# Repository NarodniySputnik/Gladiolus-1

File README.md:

# Проект Gladiolus-1 (Народный Спутник)
<div align="center"></div>

Мы - команда радиолюбителей-энтузиастов под руководством Дмитрия R4UAB Пашкова!
В данный момент мы работаем над проектом "Народный спутник"! 
Наша цель - это создание функционального малого космического аппарата (CubeSat) для популяризации радиолюбительства, как интересного и увлекательного занятия для людей всех возрастов. Проект создаётся полностью на добровольных началах и заинтересованности наших участников. 

Наши задачи: 

- Реализовать полный цикл создания малого космического аппарата CubeSat - от проектирования и сборки до запуска и работы на орбите. 
- Предоставить открытые данные и существующие наработки по проекту для всех желающих, вдохновить всех любителей космической тематики и радиолюбителей на разработку и участие в новых интересных технологических проектах. 
- Объединить единомышленников для практической работы в области космических технологий и радиосвязи.

С огромнейшим удовольствием примем в нашу команду всех кто может и хочет приложить руку к созданию реального космического аппарата!

We are a team of amateur radio enthusiasts led by Dmitry "R4UAB" Pashkov!
We are currently working on the "People's Satellite" project! Our goal is to create a functional small spacecraft (CubeSat) to popularize amateur radio as an interesting and engaging activity for people of all ages. The project is being developed entirely on a voluntary basis and based on the passion of our participants.

Our goals:

- Implement the full development cycle of the CubeSat small spacecraft-from design and assembly to launch and operation in orbit.
- Provide open data and existing project developments to everyone, inspiring all space enthusiasts and radio amateurs to develop and participate in new exciting technological projects.
- Bring together like-minded individuals for practical work in the field of space technology and radio communications.

We are delighted to welcome anyone who can and wants to contribute to the creation of a real spacecraft to our team!

## Структура директорий
- doc - Документы
	- ds - Технические спецификации
	- img - Изображения
	- info - Информация
	- ref - Референсы и примеры
- firmware - Прошивки
- hardware - Печатные платы и схемы
	- library - Библиотеки KiCad
- software - Программы

## Назначение модуля
Gladiolus-1 - автономный модуль для приема и передачи изображений в формате SSTV (Slow Scan TeleVision) на малом космическом аппарате (МКА) формата CubeSat

1.2. Основание для разработки
Решение технического комитета проекта «Gladiolus-1» 

1.3. Назначение
Создание функциональной полезной нагрузки для:

Приёма команд с Земли <br>
Съёмки поверхности Земли <br>
Генерации и передачи изображений в формате SSTV <br>
Приёма и ретрансляции цифровых пакетных данных <br>
Проведения образовательных и научных экспериментов

1.4. Краткое описание системы<br>
Полезная нагрузка представляет собой модульную систему, построенную на основе единой шинной архитектуры. Система включает в себя два вычислительных блока различной архитектуры, обеспечивающих резервирование и распределение функций, два идентичных модемных блока с возможностью взаимозамены, центральный блок управления питанием и данными, а также антенную систему.

2. ОБЩИЕ ТРЕБОВАНИЯ

2.1. Эксплуатационные характеристики

<div align="left">
<table>
<tr><td>Формат:</td><td>CubeSat 1U (габариты 100×100×113,5 мм)</td></tr>
<tr><td>Орбита:</td><td>Низкая околоземная орбита (высота 500–600 км), солнечно-синхронная</td></tr>
<tr><td>Энергопотребление среднее:</td><td>не более 2Вт</td></tr>
<tr><td>Энергопотребление пиковое:</td><td>Не более 5Вт</td></tr>
<tr><td>Масса:</td><td>Не более 1.33кг</td></tr>
<tr><td>Габариты:</td><td>Соответствуют стандарту CubeSat 1U</td></tr>
</table></div>
Режимы работы должны обеспечивать положительный энергобаланс

2.2. Условия эксплуатации

<div align="left">
<table>
<tr><td>Температурный диапазон:</td><td>–40°C до +80°</td></tr>
<tr><td>Вибронагрузки:</td><td>Соответствуют стандартам запуска CubeSat</td></tr>
<tr><td>Ударные нагрузки:</td><td>До 100g</td></tr>
<tr><td>Вакуум:</td><td>До 10⁻⁶ Торр</td></tr>
<tr><td>Радиационная стойкость:</td><td>Критическая накопленная доза облучения 20 крад (Si)</td></tr>
</table></div>

2.3. Интерфейсы с платформой спутника
<div align="left"><table>
<tr><td>Питание:</td><td>Напряжение шины питания 3.2-8.4 В, ток до 1 А</td></tr>
<tr><td>Механический интерфейс:</td><td>Стандартные крепления CubeSat</td></tr>
<tr><td>Тепловой интерфейс:</td><td>Кондуктивный отвод тепла на платформу</td></tr>
<tr><td>Другие интерфейсы:</td><td>Не предусмотрены</td></tr>

</table></div>

3. ФУНКЦИОНАЛЬНОЕ ДЕЛЕНИЕ И ТРЕБОВАНИЯ К БЛОКАМ

3.1. БЦВМ 1 (Бортовая Цифровая Вычислительная Машина 1)

3.1.1. Аппаратная платформа:

<div align="left"><table>
<tr><td>Основной процессор:</td><td>Raspberry Pi Zero v1.3</td></tr>
<tr><td>Память:</td><td>Оперативная 512 МБ, флеш-память microSD</td></tr>
<tr><td>Тактовая частота:</td><td>Программно регулируемая от минимальной до номинальной</td></tr>
<tr><td>Отключаемые интерфейсы:</td><td>USB, HDMI, ненужные периферийные модули</td></tr>
</table></div>

3.1.2. Функции:

<div align="left">
<table>
<tr><td>Управление файловой системой бортового накопителя</td></tr>
<tr><td>Общее управление системой и координация работы блоков</td></tr>
<tr><td>Обработка команд и телеметрии</td></tr>
<tr><td>Маршрутизация данных между подсистемами</td></tr>
<tr><td>Резервная функция программной генерации сигнала SSTV</td></tr>
<tr><td>Ведение журнала работы системы</td></tr>
</table></div>

3.1.3. Интерфейсы:

<div align="left">
<table>
<tr><td>1× 40-контактный разъем для подключения к материнской плате</td></tr>
<tr><td>Поддержка шин RS-485 и I2C</td></tr>
</table></div>

3.2. БЦВМ 2 (Бортовая Цифровая Вычислительная Машина 2)

3.2.1. Аппаратная платформа: <br>
Основной микроконтроллер: STM32 серии (конкретная модель по результатам анализа) <br>
Периферия: <br>
Встроенный RTC с независимым питанием <br>
Интерфейс DCMI для подключения камеры <br>
2× UART для шин RS-485 <br>
Интерфейсы I2C, SPI для дополнительной периферии <br>
Внешняя SPI-Flash или SD-карта для хранения данных <br>
Режимы работы: Поддержка энергоэффективных режимов <br>

3.2.2. Функции:
Управление камерой: инициализация, захват кадра, настройка параметров <br>
Обработка изображений и подготовка данных для передачи в формате SSTV <br>
Управление SSTV-передатчиком <br>
Синхронизация операций по времени с помощью RTC <br>
Дублирующее управление бортовым накопителем <br>
Резервирование критических функций БЦВМ 1 <br>

3.2.3. Взаимодействие между БЦВМ:
Обмен данными через единые шины RS-485 <br>
Взаимный мониторинг состояния и работоспособности <br>
Автоматическое перераспределение функций при отказах <br>
Синхронизация времени и планирование задач

3.3. Модемный блок (в количестве 2 шт.)
3.3.1. Аппаратная основа:

<div align="left"><table>
<tr><td>Радиомодули:</td><td>На каждый блок: Ra-02 (на основе SX1278)</td></tr>
<tr><td>Усилители:</td><td>МШУ на приём, усилитель AB-IOT-433 передачу</td></tr>
<tr><td>Фильтры:</td><td>ПАВ-фильтры на приём и передачу</td></tr>
<tr><td>Согласующие цепи:</td><td>Wideband matching networks</td></tr>
<tr><td>Микроконтроллер:</td><td>MSP430FR5994IPNR</td></tr>
</table></div>

3.3.2. Функциональное назначение:

<div align="left">
<table>
<tr><td>Радиомодуль 1:</td><td>SSTV передатчик (ЧМ модуляция, 438МГц)</td></tr>
<tr><td>Радиомодуль 2:</td><td>Цифровая радиолиния (435Мгц)</td></tr>
<tr><td>Резервирование:</td><td>Возможность переконфигурации модулей</td></tr>
</table></div>

3.3.3. Электрические параметры:

<div align="left">
<table>
<tr><td>Мощность передатчика:</td><td>До 2Вт (регулируемая)</td></tr>
<tr><td>Чувствительность приёмника:</td><td>Не хуже -130dBm</td></tr>
<tr><td>Стабильность частоты:</td><td>±1 ppm</td></tr>
<tr><td>Потребляемый ток:</td><td>Передача ≤ 500 мА, прием ≤ 50 мА</td></tr>
</table></div>

3.3.4. Дополнительные функции:
Контроль температуры через I2C<br>
Мониторинг параметров усилителей<br>
Защита от КЗ и перегрева<br>
Автоматическая калибровка

3.4. Материнский блок (Блок управления питанием и данными)

3.4.1. Система питания:

<div align="left"><table>
<tr><td>Вход:</td><td>3.2-8.4В от платформы спутника</td></tr>
<tr><td>Выход:</td><td>Стабилизированное +5В через интеллектуальные ключи</td></tr>
<tr><td>КПД:</td><td>Не менее 90% при номинальной нагрузке</td></tr>
<tr><td>Защите:</td><td>Ограничение тока, защита от КЗ, от перенапряжения</td></tr>
</table></div>

3.4.2. Управление и мониторинг:

<div align="left">
<table>
<tr><td>Централизованный сбор телеметрии через I2C</td></tr>
<tr><td>Управление питанием каждого блока</td></tr>
<tr><td>Аппаратный watchdog (MAX6301)</td></tr>
<tr><td>Счетчик перезагрузок в энергонезависимой памяти</td></tr>
</table></div>

3.4.3. Интерфейсы:

<div align="left">
<table>
<tr><td>4× 40-контактных разъема для функциональных блоков</td></tr>
<tr><td>2× шины RS-485 с протоколом AX.25</td></tr>
<tr><td>Шина I2C с мультиплексором для изоляции подключенных блоков</td></tr>
</table></div>

3.4.4. Система I2C мультиплексирования:
Архитектура: Мультиплексор I2C с 8 и более каналами

Назначение каналов:

<div align="left">
<table>
<tr><td>Канал 0:</td><td>Внутренние датчики материнского блока</td></tr>
<tr><td>Канал 1:</td><td>БЦВМ</td></tr>
<tr><td>Канал 2:</td><td>БЦВМ</td></tr>
<tr><td>Канал 3:</td><td>Модемный блок 1</td></tr>
<tr><td>Канал 4:</td><td>Модемный блок 2</td></tr>
<tr><td>Канал 5:</td><td>Резерв</td></tr>
<tr><td>Канал 6:</td><td>Резерв</td></tr>
<tr><td>Канал 7:</td><td>Резерв</td></tr>
</table></div>

<div align="left">
<table>
<tr><td>Управление:</td><td>Программное переключение каналов мультиплексора</td></tr>
<tr><td>Восстановление:</td><td>Автоматический сброс зависших устройств</td></tr>
</table></div>

3.4.5. Мониторинг питания: <br>
Детектирование аварий: Мониторинг напряжения на линии PWR_FAULT <br>
Реакция на аварии: Автоматическое отключение питания блока при аварии <br>
Логирование: Запись событий аварий питания

3.5. Антенный блок
<div align="left"><table>
<tr><td>Диапазоны:</td><td>435 и 438МГц</td></tr>
<tr><td>Поляризация:</td><td>Линейная</td></tr>
<tr><td>КСВ:</td><td>Не более 1.5 в рабочем диапазоне</td></tr>
<tr><td>Конструктив:</td><td>Складываемая конструкция, совместимая с 1U CubeSat</td></tr>
<tr><td>Коэффициент усиления:</td><td>Не менее 0 dBi для каждого диапазона</td></tr>
<td>Диаграмма направленности:</td><td>Широконаправленная для обеспечения связи при различных ориентациях спутника</td></tr>
</table></div>

3.6. Требования к унификации блоков

3.6.1. Стандартизация разъемов:<br>
Единый 40-контактный разъем для всех блоков <br>
Фиксированная распиновка (см. Таблицу 1) <br>
Механическая фиксация от самопроизвольного отключения

Таблица 1. Распиновка 40-контактного разъема
<div align="left">
<table>
<tr>
<th>Контакты</th><th>Назначение</th><th>Описание</th></tr>
<tr><td>1-4</td><td>+5V</td><td>Питание +5В</td></tr>
<tr><th>5-8</th><th>GND</th><th>Земля</th></tr>
<tr><td>I2C</td><td>SCL</td><td>SCL</td></tr>
<tr><td>I2C</td><td>SDA</td><td>SDA</td></tr>
<tr><td>I2C_PWR</td><td></td><td>Плюс питания</td></tr>
<tr><td>I2C_GND</td><td></td><td>Земля</td></tr>
<tr><td>A1, B2</td><td>RS-485</td><td>2 контакта</td></tr>
<tr><td>PWR_EN</td><td>управление</td><td>включение питания</td></tr>
<tr><td>RESET</td><td>Сброс</td><td>включение питания</td></tr>
<tr><td>PWR_FAULT</td><td>Мониторинг</td><td>1 контакт</td></tr>
<tr><td>PWR_FAULT</td><td>Резерв</td><td>21 контакт</td></tr>
</table></div>

3.6.2. Организация шин:<br>
Параллельное подключение всех блоков к общим шинам<br>
Индивидуальное управление питанием<br>
Единые протоколы обмена

4. ТРЕБОВАНИЯ К ИНТЕРФЕЙСАМ И ПРОТОКОЛАМ

4.1. Физический уровень
RS-485: Двухпроводная дифференциальная шина<br>
Скорость: 1200-2000000 бод<br>
I2C: Стандартный протокол с тактовой частотой до 400 кГц (Fast Mode)

<div align="left"><table>
<tr><td>RS-485</td><td>Двухпроводная дифференциальная шина</td></tr>
<tr><td>Скорость:</td><td>1200-2000000 бод</td></tr>
<tr><td>I2C</td><td>Стандартный протокол с тактовой частотой до 400 кГц</td></tr>
</table></div>

4.2. Протокол обмена

<div align="left"><table>
<tr><td>Базовый протокол</td><td>AX.25</td></tr>
<tr><td>Формат пакетов</td><td>HDLC-like frame structure</td></tr>
<tr><td>Контроль ошибок</td><td>CRC-16</td></tr>
<tr><td>Адресация</td><td>расширенная схема адресации подсистем</td></tr>
</table></div>

4.3. Логика работы <br>
Широковещательная и адресная передача <br>
Подтверждение приема критических команд <br>
Повторная передача при ошибках <br>
Приоритезация пакетов

4.4. Протокол обмена по I2C

<div align="left"><table><tr>
<td>Адресация устройств</td><td>7-битная схема адресации</td></tr>
<tr><td>Скорость обмена</td><td>до 400 кбит/сек</td></tr>
<tr><td>Формат сообщений</td><td>Управляющие команды <br> Данные телеметрии <br> Статусные сообщения</td></tr>
<tr><td>Арбитраж</td><td>Автоматическое разрешение коллизий</td></tr>
<tr><td>Таймауты</td><td>Защита от зависания шины</td></tr>
</table></div>

5. МЕХАНИЧЕСКИЕ И КОНСТРУКТИВНЫЕ ТРЕБОВАНИЯ

5.1. Компоновка

<div align="left"><table>
<tr><td>Формат</td><td>1U CubeSat (100x100x113, 5мм)</td></tr>
<tr><td>Количество плат:</td><td>3-4 печатных платы в стэке</td></tr>
<tr><td>Высота компонентов:</td><td>С учётом зазора между платами</td></tr>
</table></div>

5.2. Материалы

<div align="left"><table>
<tr><td>Основа плат:</td><td>FR-4 c Tg ≥ 170°C</td></tr>
<tr><td>Покрытие:</td><td>Конформное покрытие для защиты от влаги и загрязнений</td></tr>
<tr><td>Защитные покрытия:</td><td>Использование металлов без защитного покрытия не допускается. Все металлические поверхности должны иметь защитное покрытие для функционирования в космических условиях</td></tr>
<tr><td>Монтажные компоненты:</td><td>Использование оловянно-свинцовых припоев (Sn63Pb37 или аналог). Бессвинцовые припои не допускаются.</td></tr>
</table></div>

5.3. Тепловой режим <br>
Пассивное охлаждение через корпус<br>
Распределение тепловыделяющих компонентов<br>
Тепловой контакт с платформой спутника

6. ТРЕБОВАНИЯ К НАДЁЖНОСТИ

6.1. Показатели надежности

<div align="left">
<table>
<tr><td>Средняя наработка на отказ:</td>
<td>≥ 10 000 часов</td></tr>
<tr><td>Вероятность безотказной работы:</td>
<td>≥ ≥ 0.95 за 1 год</td></tr>
<tr><td>Коэффициент готовности:</td>
<td>≥ 0.98</td></tr>
</table></div>

6.2. Радиационная стойкость

6.2.1. Критерии стойкости: <br>
Сохранение работоспособности до 20 крад (Si)<br>
Постепенная деградация параметров после 20 крад<br>
Сохранение базовой функциональности до 25 крад

6.2.2. Методы обеспечения: <br>
Выбор компонентов с подтвержденной стойкостью<br>
Локальные экраны для чувствительных элементов<br>
Схемная избыточность и резервирование<br>
RAD-HARD компоненты для критических узлов

6.2.3. Испытания: <br>
Радиационные испытания на ускорителях<br>
Контроль параметров при дозах 10, 15, 20, 25 крад<br>
Тестирование на SEE и SEL<br>
Термоциклирование после облучения

6.2.4. Расчетные параметры: <br>
Запас 20% относительно расчетной дозы<br>
Учет всех видов ионизирующего излучения<br>
Моделирование радиационной обстановки

7. ТРЕБОВАНИЯ К ОТЛАДОЧНОМУ ОБОРУДОВАНИЮ

7.1. Плата-удлинитель для внешней отладки

7.1.1. Конструкция: <br>
Печатная плата с посадочным местом для функционального блока<br>
Штатный 40-контактный разъем со стороны спутника<br>
Механическое крепление блока винтами<br>
Тестовые точки и защитные элементы

7.1.2. Параметры: <br>
Сопротивление проводников: ≤ 0.1 Ом
Рабочая температура: -40°C до +80°C
Стойкость к вибрациям согласно требованиям

<div align="left"><table>
<tr><td>Сопротивление проводников:</td><td> ≤ 0.1 Ом</td></tr>
<tr><td>Рабочая температура:</td><td>-40°C до +80°C</td></tr>
<tr><td>Стойкость к вибрациям:</td><td>Cогласно требованиям</td></tr>
</table></div>

7.2. Плата-эмулятор материнской платы <br>
7.2.1. Функционал:
Эмуляция штатной материнской платы<br>
Управление питанием подключенного блока<br>
Мониторинг токопотребления<br>
Организация шин RS-485 и I2C

7.2.2. Интерфейсы: <br>
1× 40-контактный разъем для блока<br>
USB Type-C для питания и связи<br>
JTAG для низкоуровневой отладки<br>

7.2.3. Программное обеспечение: <br>
Графическая утилита для управления<br>
Эмуляция штатных режимов работы<br>
Логирование и анализ данных<br>
Библиотека тестовых сценариев<br>
Мониторинг шины I2C в реальном времени

7.2.4. Технические характеристики:

<div align="left"><table>
<tr><td>Входное напряжение</td><td>12 В DC или USB-C</td></tr>
<tr><td>Выходной ток</td><td>До 2А</td></tr>
<tr><td>Поддержка скоростей RS-485:</td><td>1200 бод - 2 Мбод</td></tr>
<tr><td>Поддержка I2C:</td><td>Standard Mode (100 кГц), Fast Mode (400 кГц)</td></tr>
<tr><td>Рабочая температура:</td><td>0°C до +50°C</td></tr>
</table></div>

7.3. Совместимость <br>
Полная электрическая и программная совместимость<br>
Использование в термовакуумной камере<br>
Соответствие требованиям наземных испытаний

8. ЭТАПЫ РАЗРАБОТКИ И ИСПЫТАНИЙ

8.1. Основные этапы <br>
Эскизное проектирование<br>
Разработка конструкторской документации<br>
Изготовление опытных образцов<br>
Проведение испытаний<br>
Изготовление летного образца<br>
Сопровождение запуска и эксплуатации

8.2. Виды испытаний <br>
Вибродинамические<br>
Термовакуумные<br>
Радиационные<br>
Электромагнитная совместимость<br>
Функциональные и комплексные

8.3. Требования к вибродинамическим испытаниям
8.3.1. Условия проведения испытаний: <br>
Температура: +20°C ±5°C <br>
Относительная влажность: 40-60% <br>
Крепление образца: Штатные крепежные элементы, момент затяжки согласно конструкторской документации <br>

8.3.2. Режимы вибрационных испытаний:

<div align="left">
<table>
<tr><th>Синусоидальная вибрация</th></tr>
<tr><td>Диапазон частот:</td><td>5-100Гц</td></tr>
<tr><td>Амплитуда:</td><td>20g</td></tr>
<tr><td>Скорость развёртки:</td><td>2 октавы/мин</td></tr>
<tr><td>Направления:</td><td>X, Y, Z оси</td></tr>
<tr><td>Количество циклов:</td><td>3 цикла на каждое направление</td></tr>
<tr><th>Случайная вибрация</th></tr>
<tr><td>Диапазон частот:</td><td>20-2000Гц</td></tr>
<tr><td>Спектральная плотность 20-100Гц</td><td>+3 дБ/окт</td></tr>
<tr><td>Спектральная плотность 100-700Гц</td><td>0.04 g²/Гц</td></tr>
<tr><td>Спектральная плотность 700-2000Гц</td><td>-3 дБ/окт</td></tr>
<tr><td>Общее СКУ ускорение</td><td>7.7 g (среднеквадратичное)</td></tr>
<tr><td>Длительность:</td><td>2 минуты на каждое направление</td></tr>
<tr><td>Направления:</td><td>X, Y, Z оси</td></tr>
</table></div>

8.3.3. Контроль во время испытаний: <br>
Непрерывный мониторинг электрических параметров<br>
Регистрация резонансных частот<br>
Визуальный контроль после каждого этапа испытаний<

8.3.4. Критерии успешного прохождения: <br>
Отсутствие механических повреждений<br>
Сохранение функциональности системы<br>
Отсутствие необратимых изменений параметров<br>
Соответствие резонансных частот требованиям конструкции

8.4. Требования к термовакуумным испытаниям

8.4.1. Условия проведения испытаний:

<div align="left">
<table>
<tr><td>Вакуум:</td><td>≤ 10⁻⁵ Торр</td></tr>
<tr><td>Температурный диапазон:</td><td>-40°C до +80°C</td></tr>
<tr><td>Скорость изменения температуры:</td><td>не более 5°C/мин</td></tr>
<tr><td>Температурные датчики:</td><td>не менее 6 точек контроля</td></tr>
</table></div>

8.4.2. Профиль температурных циклов:

<div align="left">
<table>
<tr><th>Квалификационные испытания</th></tr>
<tr><td>Количество циклов:</td><td>8 циклов</td></tr>
<tr><td>Выдержка на экстремумах:</td><td>4 часа</td></tr>
<tr><td>Температурный диапазон:</td><td>-45°C до +85°C</td></tr>
<tr><th>Приёмо-сдаточные испытания</th></tr>
<tr><td>Количество циклов:</td><td>4 цикла</td></tr>
<tr><td>Выдержка на экстремумах:</td><td>2 часа</td></tr>
<tr><td>Температурный диапазон:</td><td>-40°C до +80°C</td></tr>
</table></div>

8.4.3. Контроль параметров: <br>
Электрические параметры: <br>
Потребляемый ток в различных режимах<br>
Стабильность напряжений питания<br>
Работоспособность интерфейсов связи<br>
Функциональные проверки:<br>
Проверка работы камеры на всех температурах<br>
Тестирование радиоканалов<br>
Проверка систем обработки данных

8.4.4. Тепловой баланс:

<div align="left"><table>
<tr><td>Мощность нагревателей:</td><td>регулируемая, с точностью ±1°C</td></tr>
<tr><td>Охлаждение:</td><td>жидкий азот или механическое охлаждение</td></tr>
<tr><td>Стабилизация температуры:</td><td>±2°C от заданной</td></tr>
</table></div>

8.4.5. Критерии успешного прохождения: <br>
Отсутствие деградации материалов и покрытий в вакууме (улетучивания, растрескивания)<br>
Сохранение герметичности компонентов<br>
Стабильность электрических параметров в течение всего цикла<br>
Отсутствие сбоев в работе программного обеспечения<br>
Сохранение механической целостности после термических расширений/сжатий<br>
Соответствие тепловых режимов расчетным значениям

## Состав команды | Team members

### Руководитель проекта | Team leader
- @r4uab

### Главный Конструктор | Chief Designer
- AnatoliySV

### Разработка антенны | Antenna development
- @stellar_alice
- @SV2HWM
- @Esprit_bel

### Разработка радиотракта | Radio path development
- @ub1qbm
- @PhaseShifting
- @ub8qbd

### Экспертная команда | Expert team
- @R2FAL
- @baskiton
- @RA3PPY

### Технические писатели | Technical writers
- @Esprit_bel

### Программисты | Programmers
- @cugadese

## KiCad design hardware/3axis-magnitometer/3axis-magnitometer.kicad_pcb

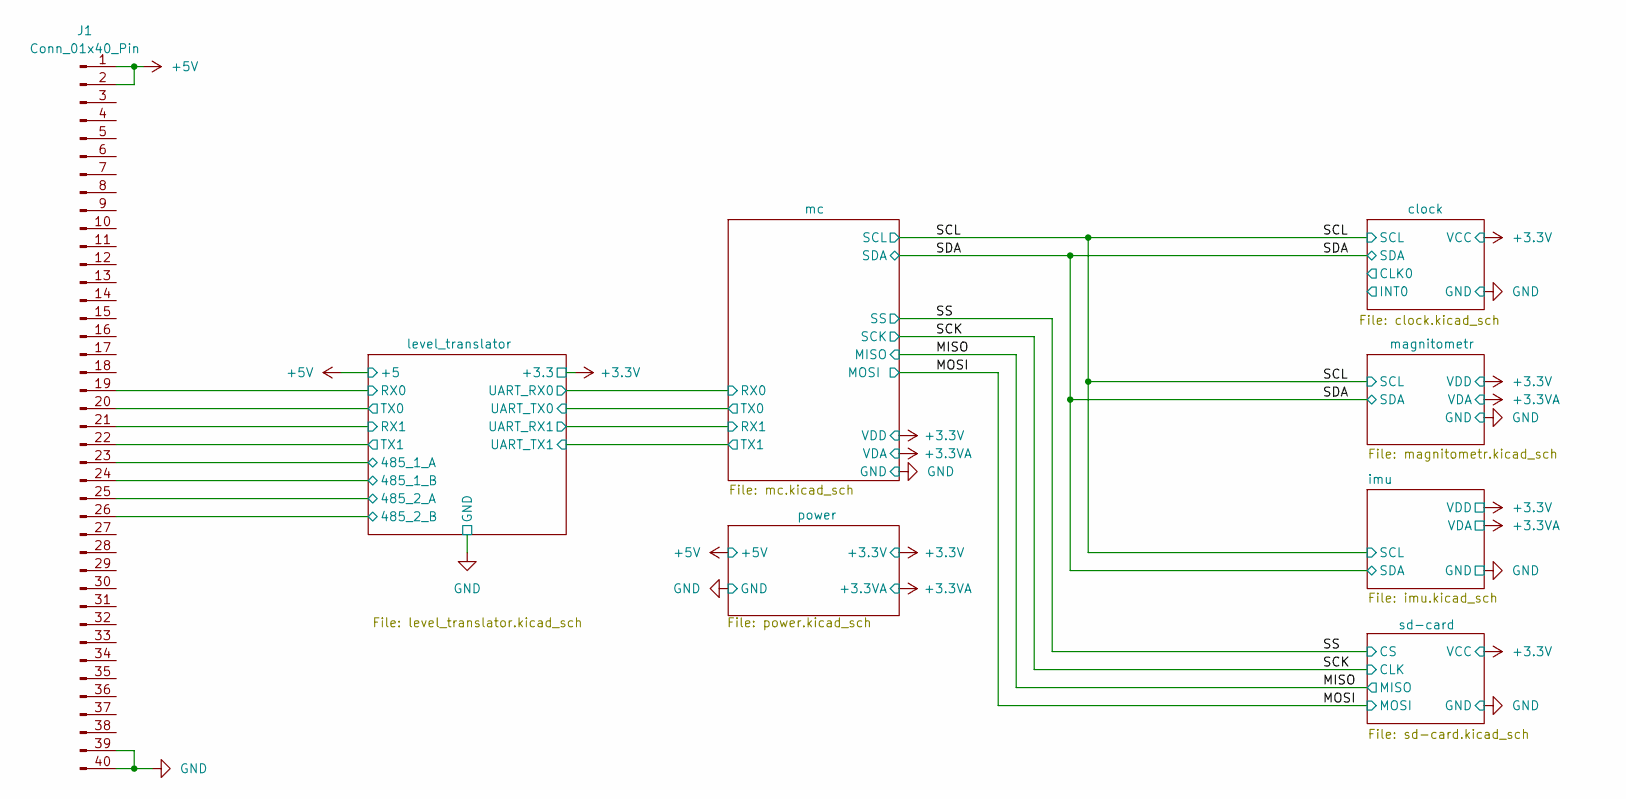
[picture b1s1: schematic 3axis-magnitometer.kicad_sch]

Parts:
J1: Conn_01x40_Pin; PinHeader_2x20_P2.54mm_Horizontal

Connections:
+5V: J1.1, J1.2; also elsewhere on the board
/level_translator/485_1_A: J1.23; also elsewhere on the board
/level_translator/485_1_B: J1.24; also elsewhere on the board
/level_translator/485_2_A: J1.25; also elsewhere on the board
/level_translator/485_2_B: J1.26; also elsewhere on the board
/level_translator/RX0: J1.19; also elsewhere on the board
/level_translator/RX1: J1.21; also elsewhere on the board
/level_translator/TX0: J1.20; also elsewhere on the board
/level_translator/TX1: J1.22; also elsewhere on the board
GND: J1.39, J1.40; also elsewhere on the board

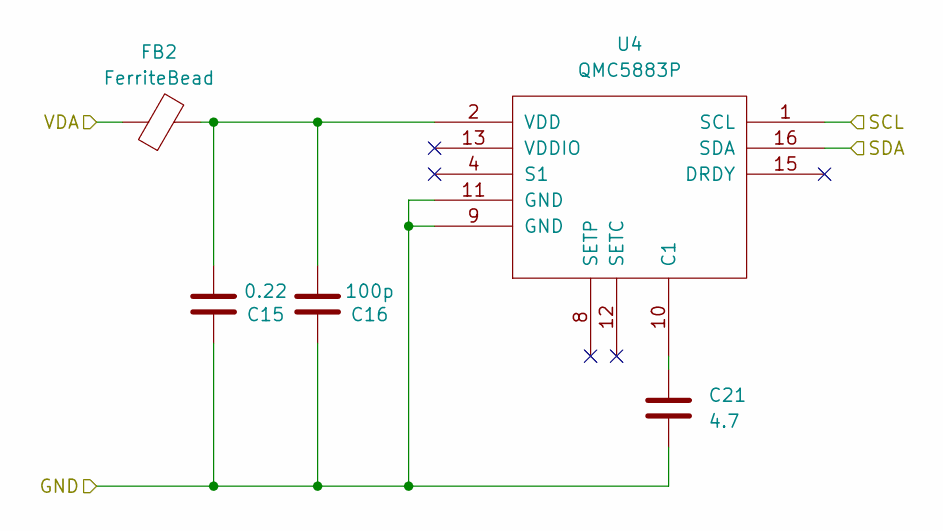
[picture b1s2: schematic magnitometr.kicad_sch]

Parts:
C15: 0.22; C_0805_2012Metric
C16: 100p; C_0805_2012Metric
C21: 4.7; C_0805_2012Metric
FB2: FerriteBead; L_0805_2012Metric
U4: QMC5883P; LGA-16_3x3mm_P0.5mm_LayoutBorder3x5y

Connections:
+3.3VA: FB2.1; also elsewhere on the board
/SCL: U4.1 (SCL); also elsewhere on the board
/SDA: U4.16 (SDA); also elsewhere on the board
GND: C15.2, C16.2, C21.2, U4.9 (GND), U4.11 (GND); also elsewhere on the board
unnamed: C21.1, U4.10 (C1)
unnamed: C15.1, C16.1, FB2.2, U4.2 (VDD)

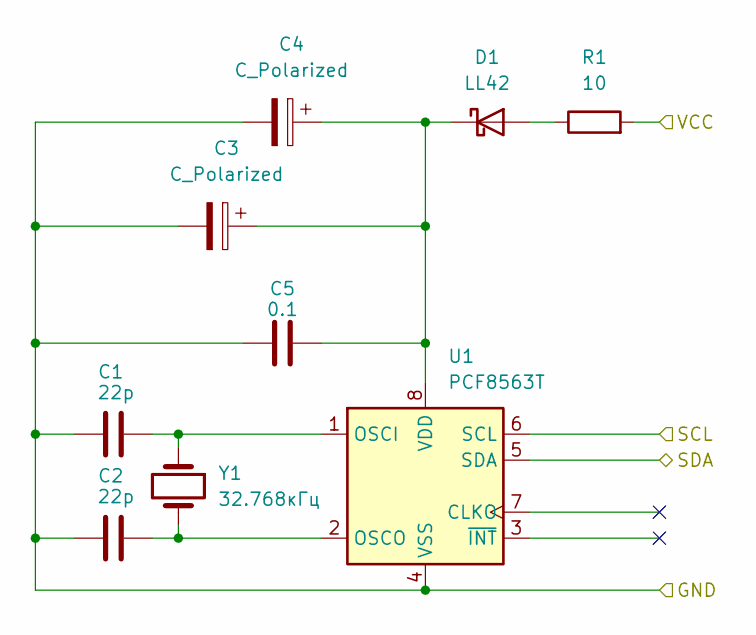
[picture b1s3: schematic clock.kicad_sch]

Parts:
C1, C2: 22p; C_0805_2012Metric
C3, C4: C_Polarized; DSK
C5: 0.1; C_0805_2012Metric
D1: LL42; D_MiniMELF
R1: 10; R_0805_2012Metric
U1: PCF8563T; SOIC-8_3.9x4.9mm_P1.27mm
Y1: 32.768кГц; Crystal_AT310_D3.0mm_L10.0mm_Horizontal_1EP_style2

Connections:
+3.3V: R1.2; also elsewhere on the board
/SCL: U1.6 (SCL); also elsewhere on the board
/SDA: U1.5 (SDA); also elsewhere on the board
GND: C1.2, C2.2, C3.2, C4.2, C5.1, U1.4 (VSS), Y1.3; also elsewhere on the board
unnamed: D1.2 (A), R1.1
unnamed: C3.1, C4.1, C5.2, D1.1 (K), U1.8 (VDD)
unnamed: C1.1, U1.1 (OSCI), Y1.1
unnamed: C2.1, U1.2 (OSCO), Y1.2

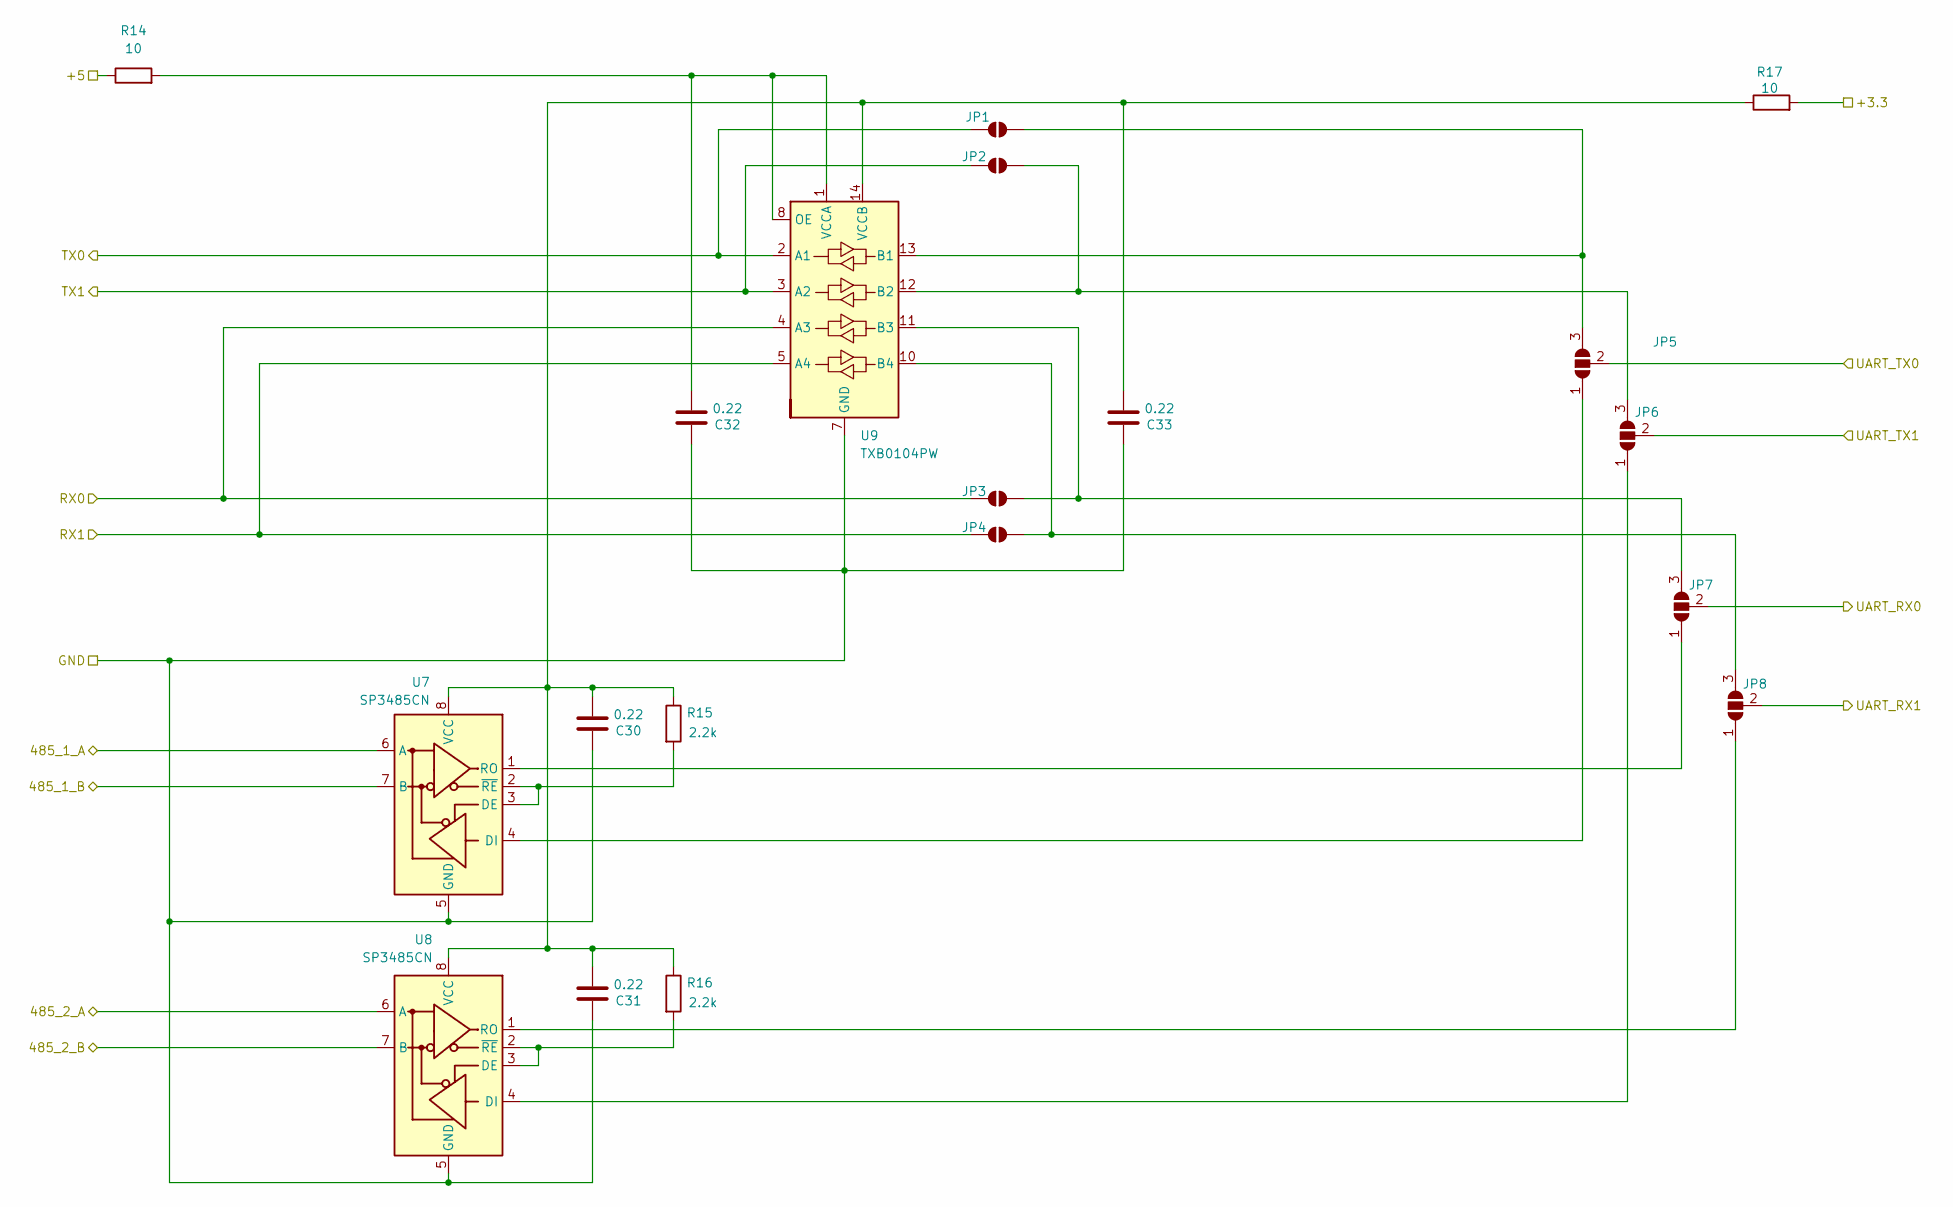
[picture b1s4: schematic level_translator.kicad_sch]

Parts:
C30, C31, C32, C33: 0.22; C_0805_2012Metric
JP1, JP2, JP3, JP4: SolderJumper_2_Open; SolderJumper-2_P1.3mm_Open_Pad1.0x1.5mm
JP5, JP6, JP7, JP8: SolderJumper_3_Open; SolderJumper-3_P1.3mm_Open_Pad1.0x1.5mm
R14, R17: 10; R_0805_2012Metric
R15, R16: 2.2k; R_0805_2012Metric
U7, U8: SP3485CN; SOIC-8_3.9x4.9mm_P1.27mm
U9: TXB0104PW; TSSOP-14_4.4x5mm_P0.65mm

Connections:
+3.3V: R17.2; also elsewhere on the board
+5V: R14.1; also elsewhere on the board
/level_translator/485_1_A: U7.6 (A); also elsewhere on the board
/level_translator/485_1_B: U7.7 (B); also elsewhere on the board
/level_translator/485_2_A: U8.6 (A); also elsewhere on the board
/level_translator/485_2_B: U8.7 (B); also elsewhere on the board
/level_translator/RX0: JP3.1 (A), U9.4 (A3); also elsewhere on the board
/level_translator/RX1: JP4.1 (A), U9.5 (A4); also elsewhere on the board
/level_translator/TX0: JP1.1 (A), U9.2 (A1); also elsewhere on the board
/level_translator/TX1: JP2.1 (A), U9.3 (A2); also elsewhere on the board
/level_translator/UART_RX0: JP7.2 (C); also elsewhere on the board
/level_translator/UART_RX1: JP8.2 (C); also elsewhere on the board
/level_translator/UART_TX0: JP5.2 (C); also elsewhere on the board
/level_translator/UART_TX1: JP6.2 (C); also elsewhere on the board
GND: C30.2, C31.2, C32.2, C33.2, U7.5 (GND), U8.5 (GND), U9.7 (GND); also elsewhere on the board
unnamed: JP1.2 (B), JP5.3 (B), U9.13 (B1)
unnamed: JP2.2 (B), JP6.3 (B), U9.12 (B2)
unnamed: JP3.2 (B), JP7.3 (B), U9.11 (B3)
unnamed: JP4.2 (B), JP8.3 (B), U9.10 (B4)
unnamed: JP5.1 (A), U7.4 (DI)
unnamed: JP6.1 (A), U8.4 (DI)
unnamed: JP7.1 (A), U7.1 (RO)
unnamed: JP8.1 (A), U8.1 (RO)
unnamed: R15.2, U7.2 (~RE), U7.3 (DE)
unnamed: C30.1, C31.1, C33.1, R15.1, R16.1, R17.1, U7.8 (VCC), U8.8 (VCC), U9.14 (VCCB)
unnamed: R16.2, U8.2 (~RE), U8.3 (DE)
unnamed: C32.1, R14.2, U9.1 (VCCA), U9.8 (OE)

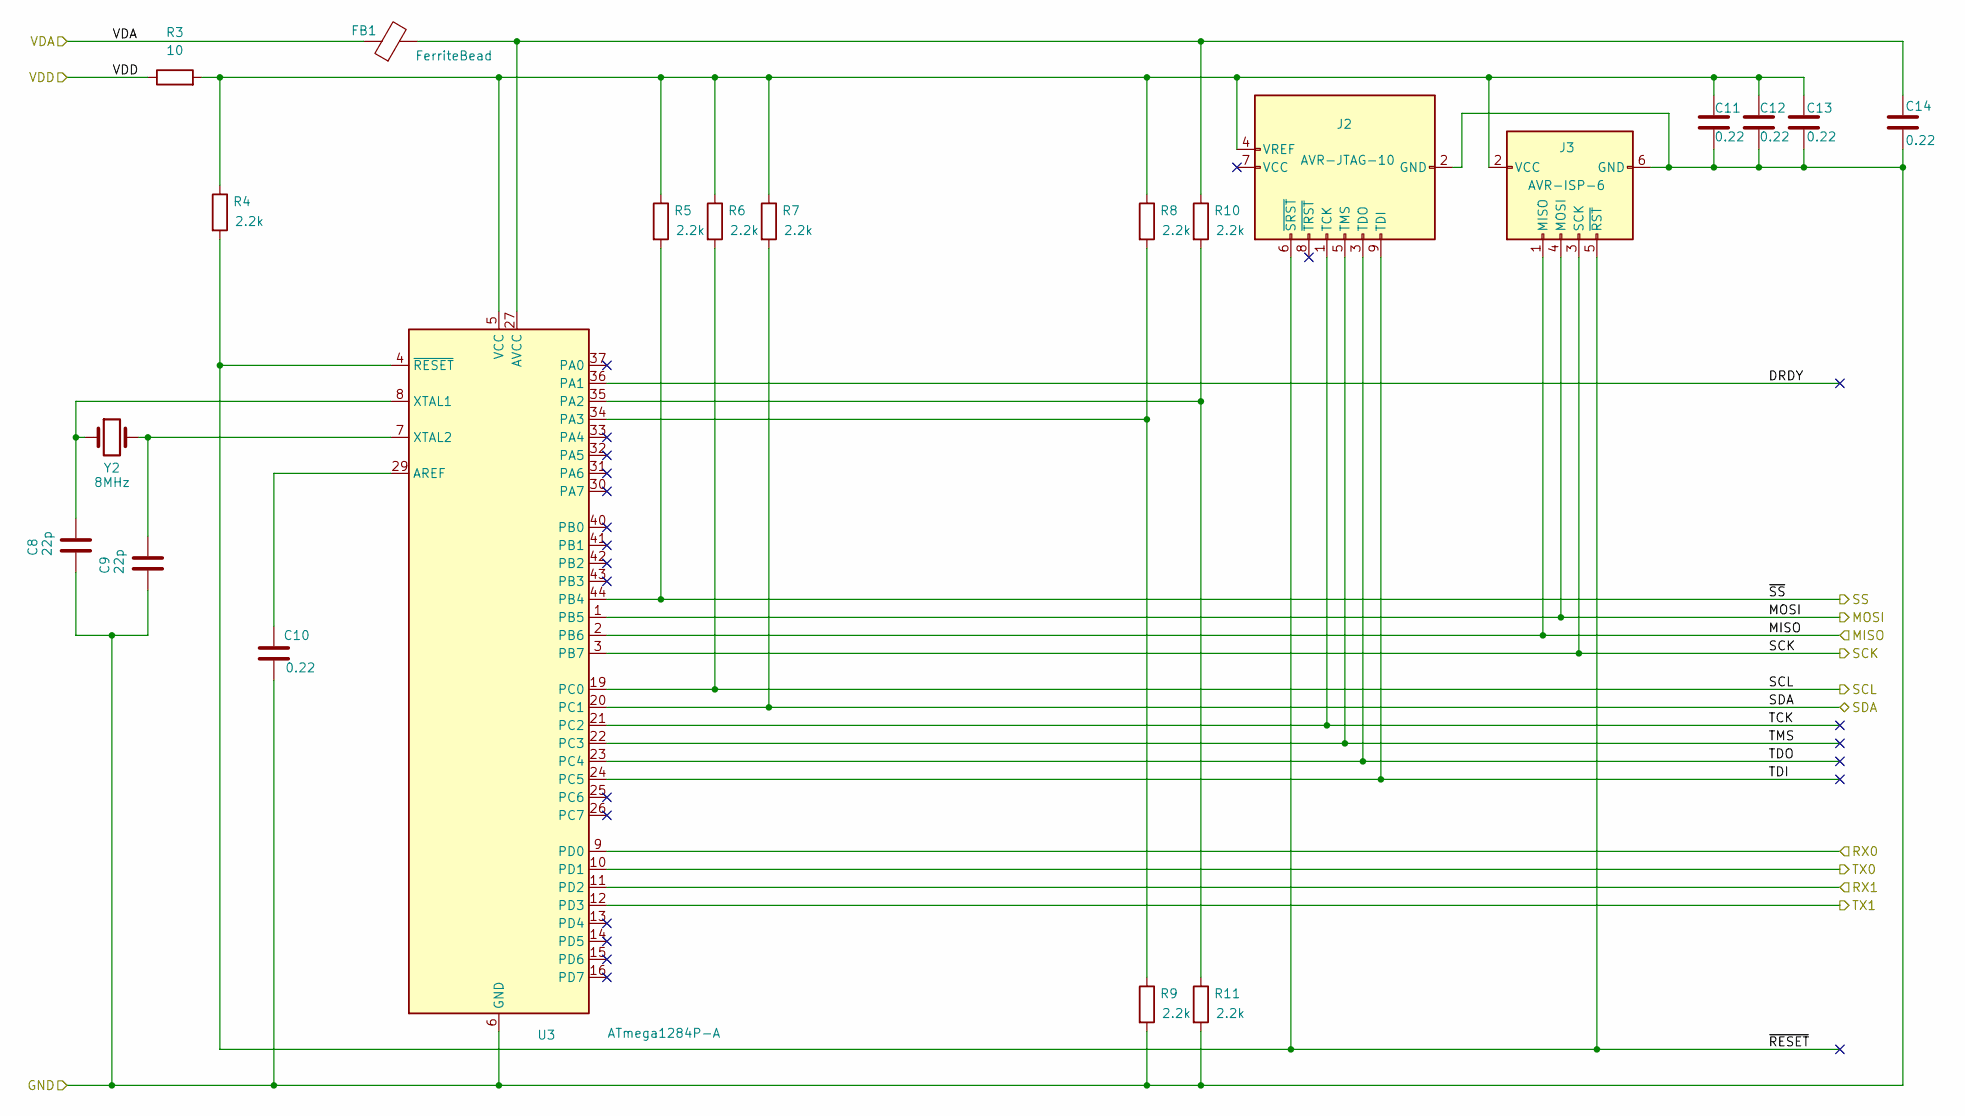
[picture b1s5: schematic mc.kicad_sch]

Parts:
C8, C9: 22p; C_0805_2012Metric
C10, C11, C12, C13, C14: 0.22; C_0805_2012Metric
FB1: FerriteBead; L_0805_2012Metric
J2: AVR-JTAG-10; PinHeader_2x05_P2.54mm_Vertical
J3: AVR-ISP-6; PinHeader_2x03_P2.54mm_Vertical
R3: 10; R_0805_2012Metric
R4, R5, R6, R7, R8, R9, R10, R11: 2.2k; R_0805_2012Metric
U3: ATmega1284P-A; TQFP-44_10x10mm_P0.8mm
Y2: 8MHz; Crystal_SMD_EuroQuartz_MQ2-2Pin_7.0x5.0mm

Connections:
+3.3V: R3.1; also elsewhere on the board
+3.3VA: FB1.1; also elsewhere on the board
/MISO: J3.1 (MISO), U3.2 (PB6); also elsewhere on the board
/MOSI: J3.4 (MOSI), U3.1 (PB5); also elsewhere on the board
/SCK: J3.3 (SCK), U3.3 (PB7); also elsewhere on the board
/SCL: R6.2, U3.19 (PC0); also elsewhere on the board
/SDA: R7.2, U3.20 (PC1); also elsewhere on the board
/SS: R5.2, U3.44 (PB4); also elsewhere on the board
/level_translator/UART_RX0: U3.9 (PD0); also elsewhere on the board
/level_translator/UART_RX1: U3.11 (PD2); also elsewhere on the board
/level_translator/UART_TX0: U3.10 (PD1); also elsewhere on the board
/level_translator/UART_TX1: U3.12 (PD3); also elsewhere on the board
/mc/DRDY: U3.36 (PA1)
/mc/TCK: J2.1 (TCK), U3.21 (PC2)
/mc/TDI: J2.9 (TDI), U3.24 (PC5)
/mc/TDO: J2.3 (TDO), U3.23 (PC4)
/mc/TMS: J2.5 (TMS), U3.22 (PC3)
/mc/~RESET: J2.6 (~SRST), J3.5 (~RST), R4.2, U3.4 (~RESET)
GND: C8.2, C9.2, C10.1, C11.1, C12.1, C13.1, C14.2, J2.2 (GND), J2.10 (GND), J3.6 (GND), R9.2, R11.2, U3.6 (GND), U3.18 (GND), U3.28 (GND), U3.39 (GND); also elsewhere on the board
unnamed: C11.2, C12.2, C13.2, J2.4 (VREF), J3.2 (VCC), R3.2, R4.1, R5.1, R6.1, R7.1, R8.1, U3.5 (VCC), U3.17 (VCC), U3.38 (VCC)
unnamed: C10.2, U3.29 (AREF)
unnamed: C14.1, FB1.2, R10.1, U3.27 (AVCC)
unnamed: R10.2, R11.1, U3.35 (PA2)
unnamed: R8.2, R9.1, U3.34 (PA3)
unnamed: C8.1, U3.8 (XTAL1), Y2.1
unnamed: C9.1, U3.7 (XTAL2), Y2.2

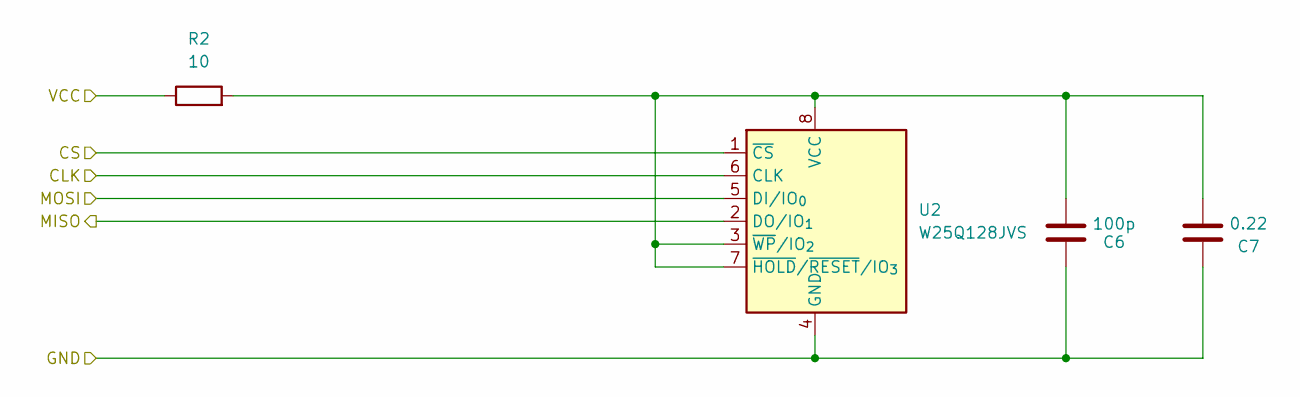
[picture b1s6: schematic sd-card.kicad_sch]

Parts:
C6: 100p; C_0805_2012Metric
C7: 0.22; C_0805_2012Metric
R2: 10; R_0805_2012Metric
U2: W25Q128JVS; SOIC-8_3.9x4.9mm_P1.27mm

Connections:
+3.3V: R2.1; also elsewhere on the board
/MISO: U2.2 (DO/IO_{1}); also elsewhere on the board
/MOSI: U2.5 (DI/IO_{0}); also elsewhere on the board
/SCK: U2.6 (CLK); also elsewhere on the board
/SS: U2.1 (~CS); also elsewhere on the board
GND: C6.1, C7.1, U2.4 (GND); also elsewhere on the board
unnamed: C6.2, C7.2, R2.2, U2.3 (~WP/IO_{2}), U2.7 (~HOLD/~RESET/IO_{3}), U2.8 (VCC)

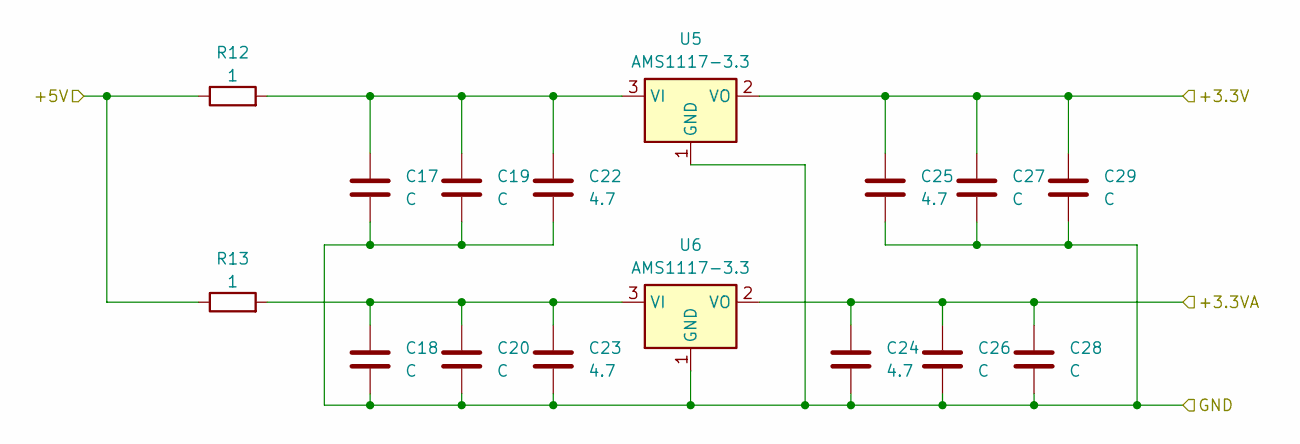
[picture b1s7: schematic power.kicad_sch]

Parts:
C17, C18, C19, C20, C26, C27, C28, C29: C; C_0805_2012Metric
C22, C23, C24, C25: 4.7; C_0805_2012Metric
R12, R13: 1; R_0805_2012Metric
U5, U6: AMS1117-3.3; SOT-223-3_TabPin2

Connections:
+3.3V: C25.1, C27.1, C29.1, U5.2 (VO); also elsewhere on the board
+3.3VA: C24.1, C26.1, C28.1, U6.2 (VO); also elsewhere on the board
+5V: R12.1, R13.1; also elsewhere on the board
GND: C17.2, C18.2, C19.2, C20.2, C22.2, C23.2, C24.2, C25.2, C26.2, C27.2, C28.2, C29.2, U5.1 (GND), U6.1 (GND); also elsewhere on the board
unnamed: C17.1, C19.1, C22.1, R12.2, U5.3 (VI)
unnamed: C18.1, C20.1, C23.1, R13.2, U6.3 (VI)

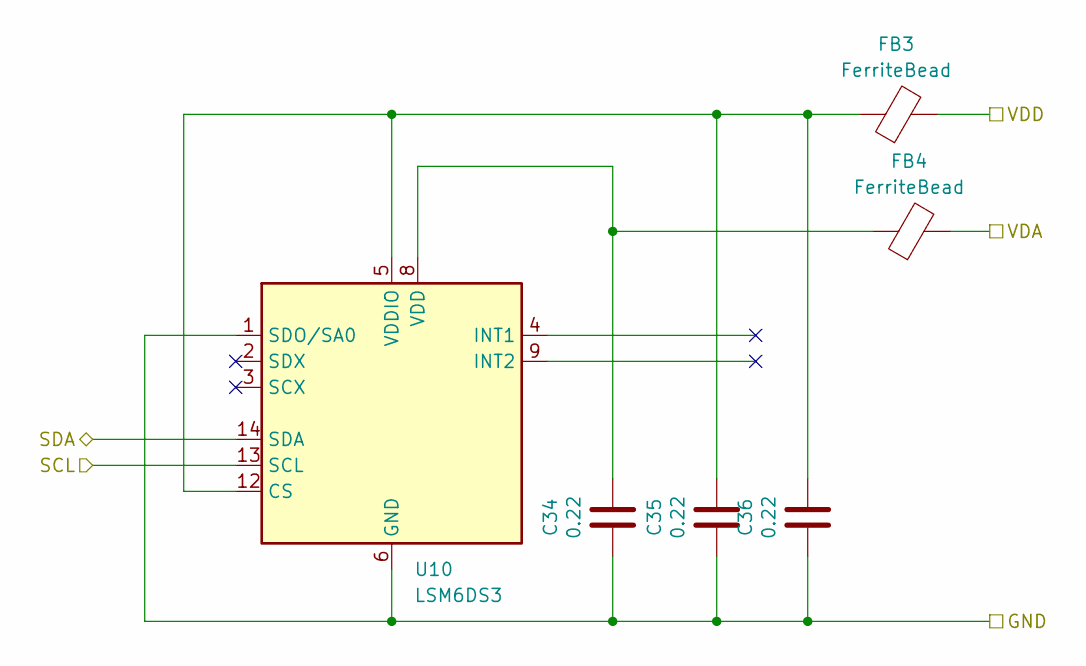
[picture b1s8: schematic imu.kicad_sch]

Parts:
C34, C35, C36: 0.22; C_0805_2012Metric
FB3, FB4: FerriteBead; L_0805_2012Metric
U10: LSM6DS3; LGA-14_3x2.5mm_P0.5mm_LayoutBorder3x4y

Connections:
+3.3V: FB3.2; also elsewhere on the board
+3.3VA: FB4.2; also elsewhere on the board
/SCL: U10.13 (SCL); also elsewhere on the board
/SDA: U10.14 (SDA); also elsewhere on the board
GND: C34.1, C35.1, C36.1, U10.1 (SDO/SA0), U10.6 (GND), U10.7 (GND); also elsewhere on the board
unnamed: C35.2, C36.2, FB3.1, U10.5 (VDDIO), U10.12 (CS)
unnamed: C34.2, FB4.1, U10.8 (VDD)

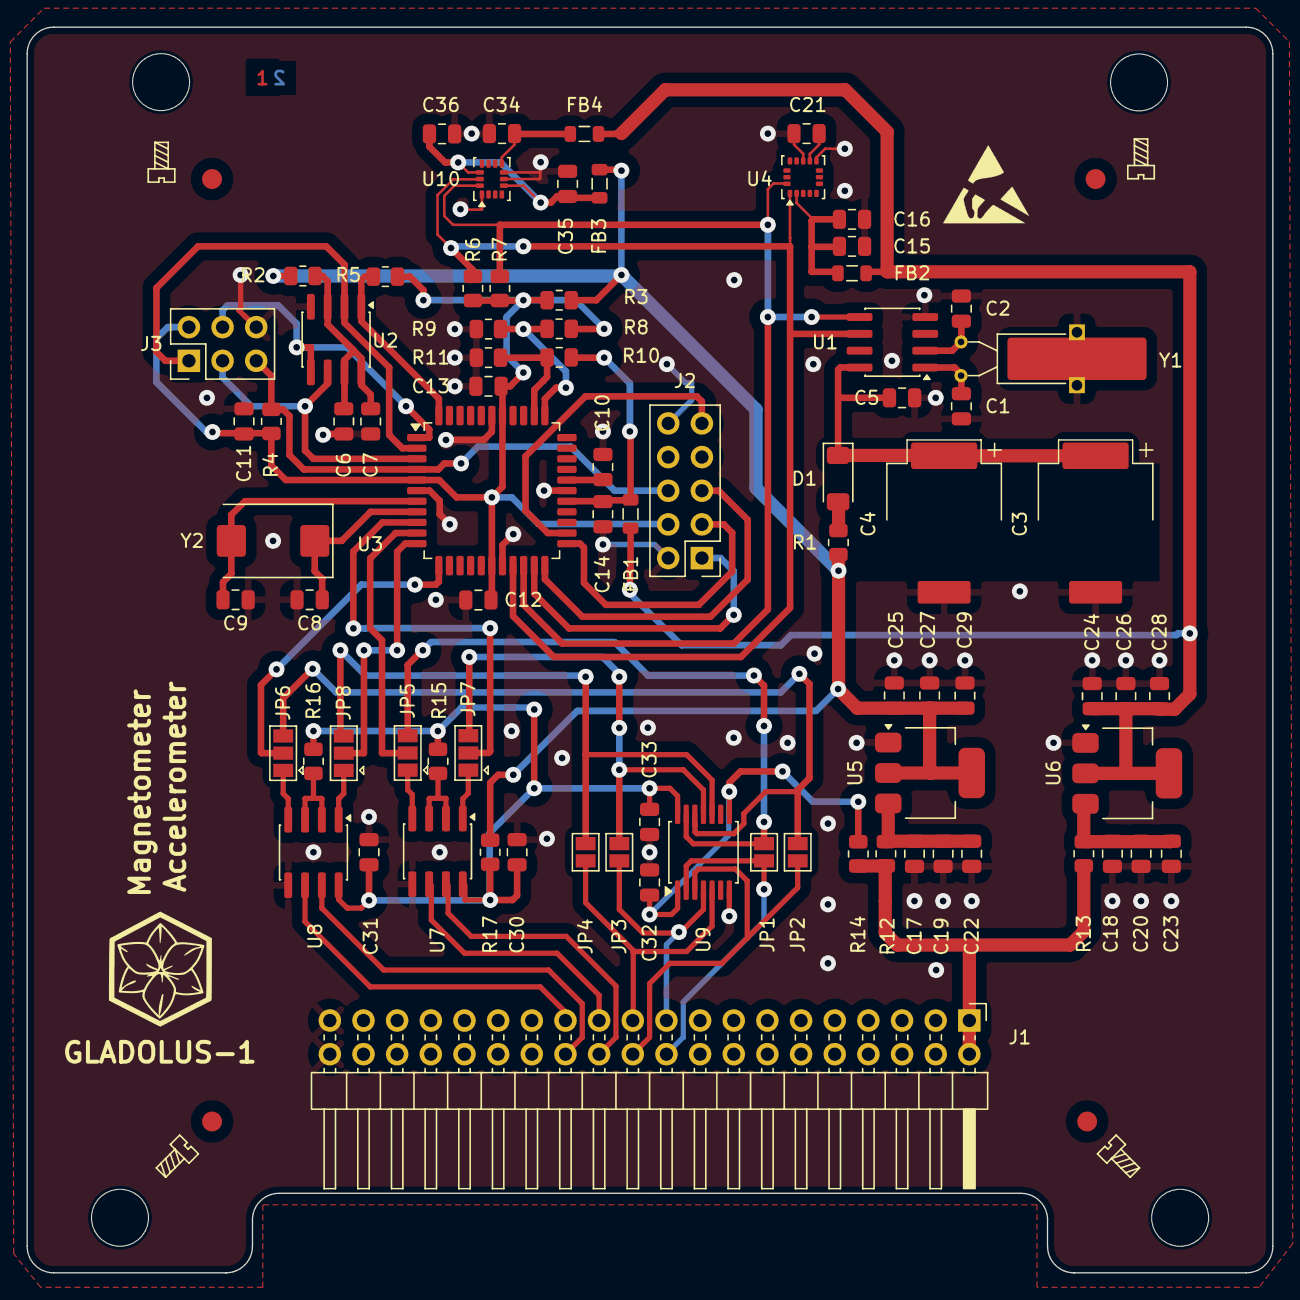
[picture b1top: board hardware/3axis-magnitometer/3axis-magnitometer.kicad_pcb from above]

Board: 2 copper layers, 94.0 x 94.0 mm, 82 parts (0 on the bottom side), 57 nets.

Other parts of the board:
GLADOLUS-1: LOGO; GLADIOLUS
